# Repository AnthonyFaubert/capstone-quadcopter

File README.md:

# capstone-quadcopter

## Note on creating code for this project
\t It will be to everyone's advantage if we alocate work to this project in different branches based on the work at hand. **DO NOT CHANGE ANYTHING ON THE MASTER BRANCH UNLESS YOU HAVE CONSULTED WITH AT LEAST TWO OTHER GROUP MEMBERS.** Let's save us all some time and sanity, and just use different branches.  Here's a cool trick to making a new branch in your command line/git bash:

```
// This creates a new branch if the name of this branch does not already exist
git branch new_branch_name_here

// This pushes your new branch to the repository (thus, you can actually push
// any changes you make to this branch to the respository).
git push --set-upstream origin new_branch_name_here 

// Switch over to working on the new branch you just made
git checkout new_branch_name_here
```

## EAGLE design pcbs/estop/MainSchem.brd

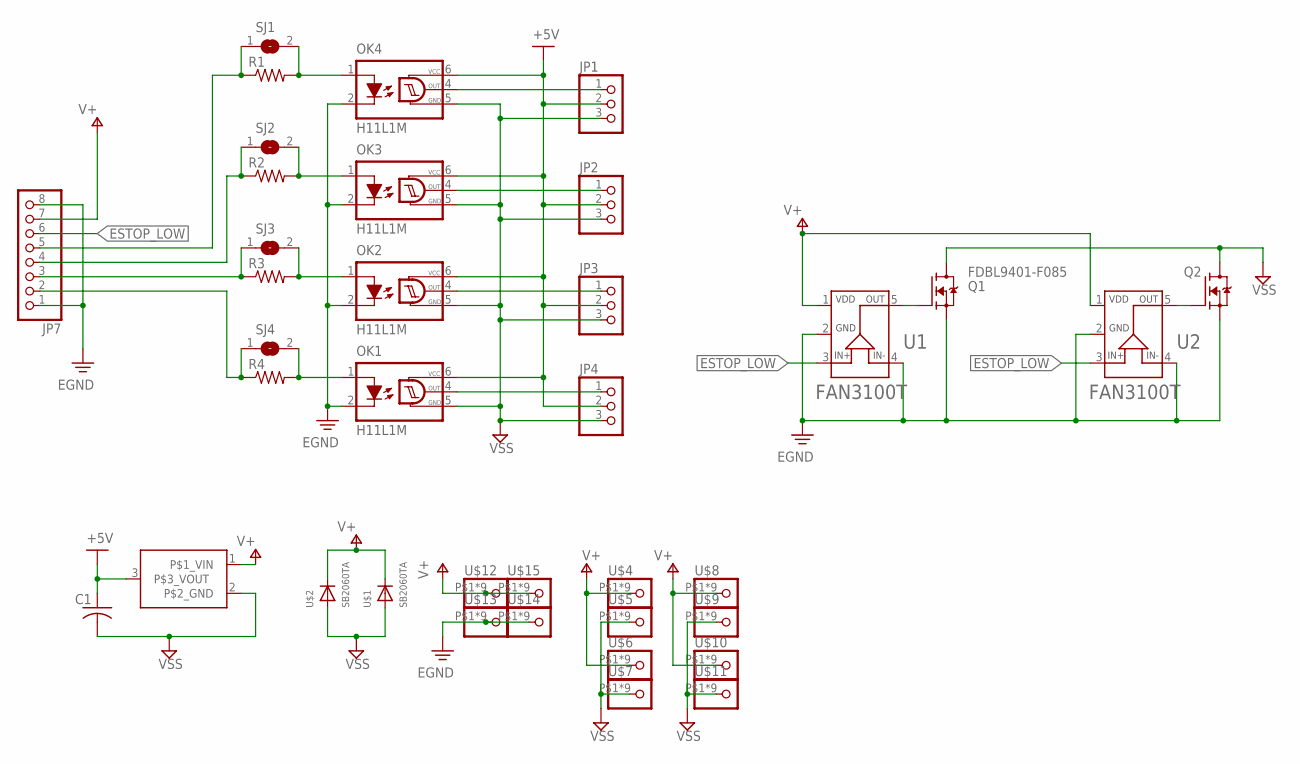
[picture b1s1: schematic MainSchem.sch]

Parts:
C1: C-US025-025X050; C025-025X050
JP1, JP2, JP3, JP4: PINHD-1X3; 1X03
JP7: PINHD-1X8_RIBBONCABLE; 1X08_RIBBONCABLE
OK1, OK2, OK3, OK4: H11L1M; DIL06
Q1, Q2: FDBL9401-F085; MOSFET_FDBL86361-F085
R1, R2, R3, R4: R-US_0204/7; 0204/7
SJ1, SJ2, SJ3, SJ4: SJ
U1, U2: FAN3100T; SOT23-5
U$1, U$2: SB2060TA; C4111-15
U$3: REGULATOR_5V; TO220
U$4, U$5, U$6, U$7, U$8, U$9, U$10, U$11, U$12, U$13, U$14, U$15: HIGH_CURRENT_WIRE_PAD

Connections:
+5V: C1.1, JP1.2, JP2.2, JP3.2, JP4.2, OK1.6 (VCC), OK2.6 (VCC), OK3.6 (VCC), OK4.6 (VCC), U$3.3 (P$3_VOUT)
EGND: JP7.1, JP7.8, OK1.2 (C), OK2.2 (C), OK3.2 (C), OK4.2 (C), Q1.2 (S), Q1.3 (S), Q1.4 (S), Q1.5 (S), Q1.6 (S), Q1.7 (S), Q1.8 (S), Q2.2 (S), Q2.3 (S), Q2.4 (S), Q2.5 (S), Q2.6 (S), Q2.7 (S), Q2.8 (S), U1.2 (GND), U1.4 (IN-), U2.2 (GND), U2.4 (IN-), U$13.P$1, U$13.P$2, U$13.P$3, U$13.P$4, U$13.P$5, U$13.P$6, U$13.P$7, U$13.P$8, U$13.P$9, U$14.P$1, U$14.P$2, U$14.P$3, U$14.P$4, U$14.P$5, U$14.P$6, U$14.P$7, U$14.P$8, U$14.P$9
ESTOP_LOW: JP7.6, U1.3 (IN+), U2.3 (IN+)
unnamed: Q2.1 (G), U2.5 (OUT)
unnamed: OK1.1 (A), R4.2, SJ4.2
unnamed: Q1.1 (G), U1.5 (OUT)
unnamed: JP4.1, OK1.4 (OUT)
unnamed: JP7.2, R4.1, SJ4.1
unnamed: JP3.1, OK2.4 (OUT)
unnamed: JP2.1, OK3.4 (OUT)
unnamed: JP1.1, OK4.4 (OUT)
unnamed: JP7.3, R3.1, SJ3.1
unnamed: OK2.1 (A), R3.2, SJ3.2
unnamed: OK3.1 (A), R2.2, SJ2.2
unnamed: JP7.4, R2.1, SJ2.1
unnamed: OK4.1 (A), R1.2, SJ1.2
unnamed: JP7.5, R1.1, SJ1.1
V+: JP7.7, U1.1 (VDD), U2.1 (VDD), U$1.C, U$2.C, U$3.1 (P$1_VIN), U$4.P$1, U$4.P$2, U$4.P$3, U$4.P$4, U$4.P$5, U$4.P$6, U$4.P$7, U$4.P$8, U$4.P$9, U$6.P$1, U$6.P$2, U$6.P$3, U$6.P$4, U$6.P$5, U$6.P$6, U$6.P$7, U$6.P$8, U$6.P$9, U$8.P$1, U$8.P$2, U$8.P$3, U$8.P$4, U$8.P$5, U$8.P$6, U$8.P$7, U$8.P$8, U$8.P$9, U$10.P$1, U$10.P$2, U$10.P$3, U$10.P$4, U$10.P$5, U$10.P$6, U$10.P$7, U$10.P$8, U$10.P$9, U$12.P$1, U$12.P$2, U$12.P$3, U$12.P$4, U$12.P$5, U$12.P$6, U$12.P$7, U$12.P$8, U$12.P$9, U$15.P$1, U$15.P$2, U$15.P$3, U$15.P$4, U$15.P$5, U$15.P$6, U$15.P$7, U$15.P$8, U$15.P$9
VSS: C1.2, JP1.3, JP2.3, JP3.3, JP4.3, OK1.5 (GND), OK2.5 (GND), OK3.5 (GND), OK4.5 (GND), Q1.9_1 (D), Q1.9_2 (D), Q1.9_3 (D), Q1.9_4 (D), Q2.9_1 (D), Q2.9_2 (D), Q2.9_3 (D), Q2.9_4 (D), U$1.A, U$2.A, U$3.2 (P$2_GND), U$5.P$1, U$5.P$2, U$5.P$3, U$5.P$4, U$5.P$5, U$5.P$6, U$5.P$7, U$5.P$8, U$5.P$9, U$7.P$1, U$7.P$2, U$7.P$3, U$7.P$4, U$7.P$5, U$7.P$6, U$7.P$7, U$7.P$8, U$7.P$9, U$9.P$1, U$9.P$2, U$9.P$3, U$9.P$4, U$9.P$5, U$9.P$6, U$9.P$7, U$9.P$8, U$9.P$9, U$11.P$1, U$11.P$2, U$11.P$3, U$11.P$4, U$11.P$5, U$11.P$6, U$11.P$7, U$11.P$8, U$11.P$9

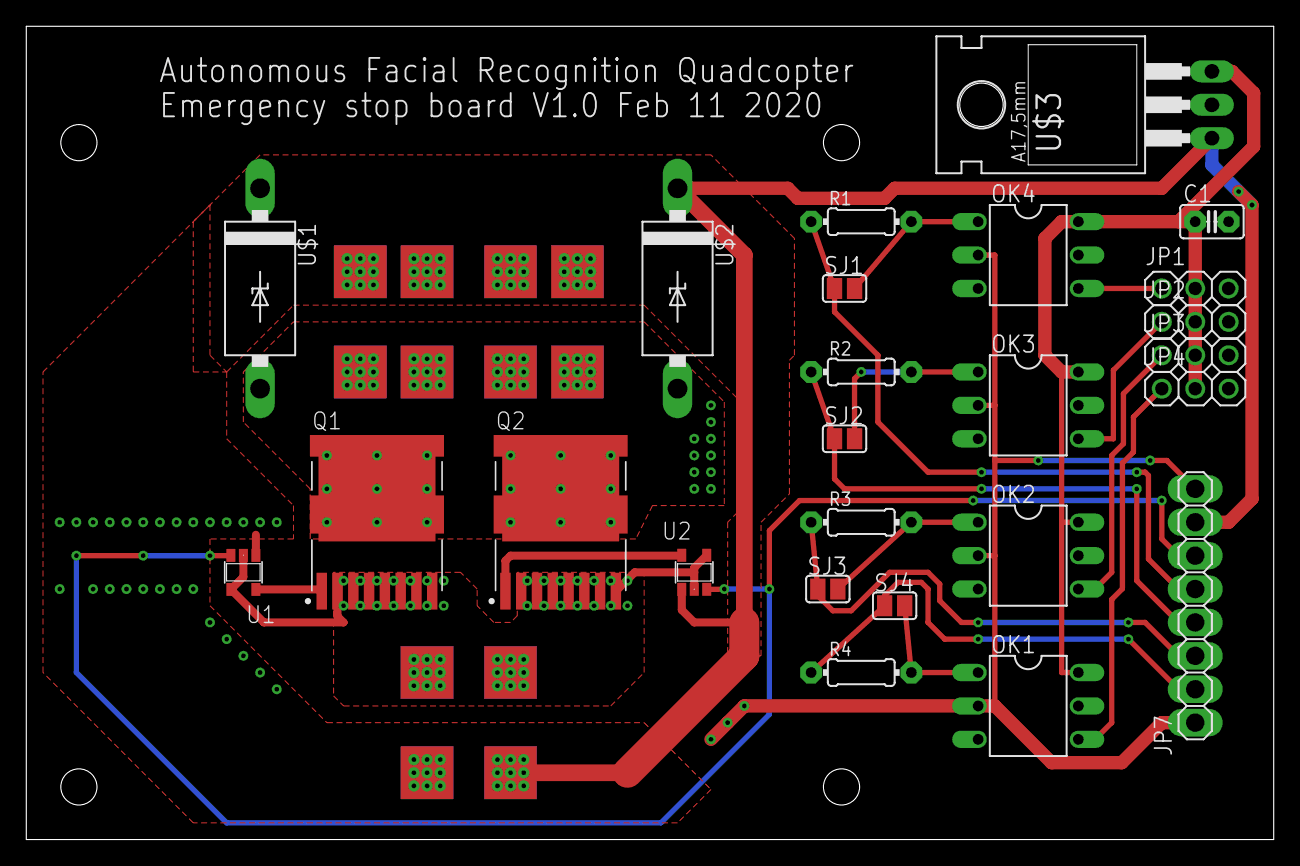
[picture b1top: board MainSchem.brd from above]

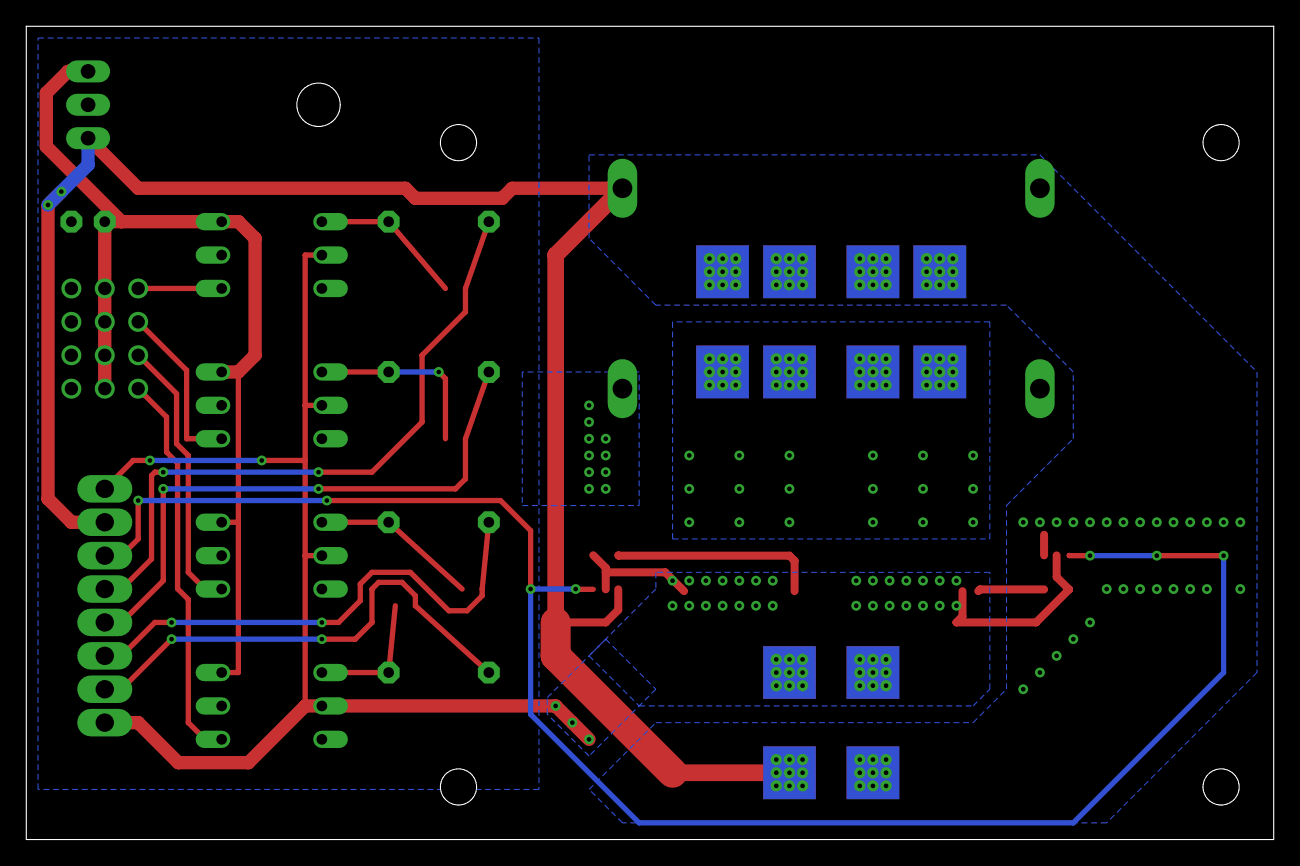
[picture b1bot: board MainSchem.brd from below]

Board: 2 copper layers, 94.9 x 61.8 mm, 41 parts (7 on the bottom side), 19 nets.

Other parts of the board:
U$16, U$17, U$18, U$19: RPI_MOUNTING_HOLE

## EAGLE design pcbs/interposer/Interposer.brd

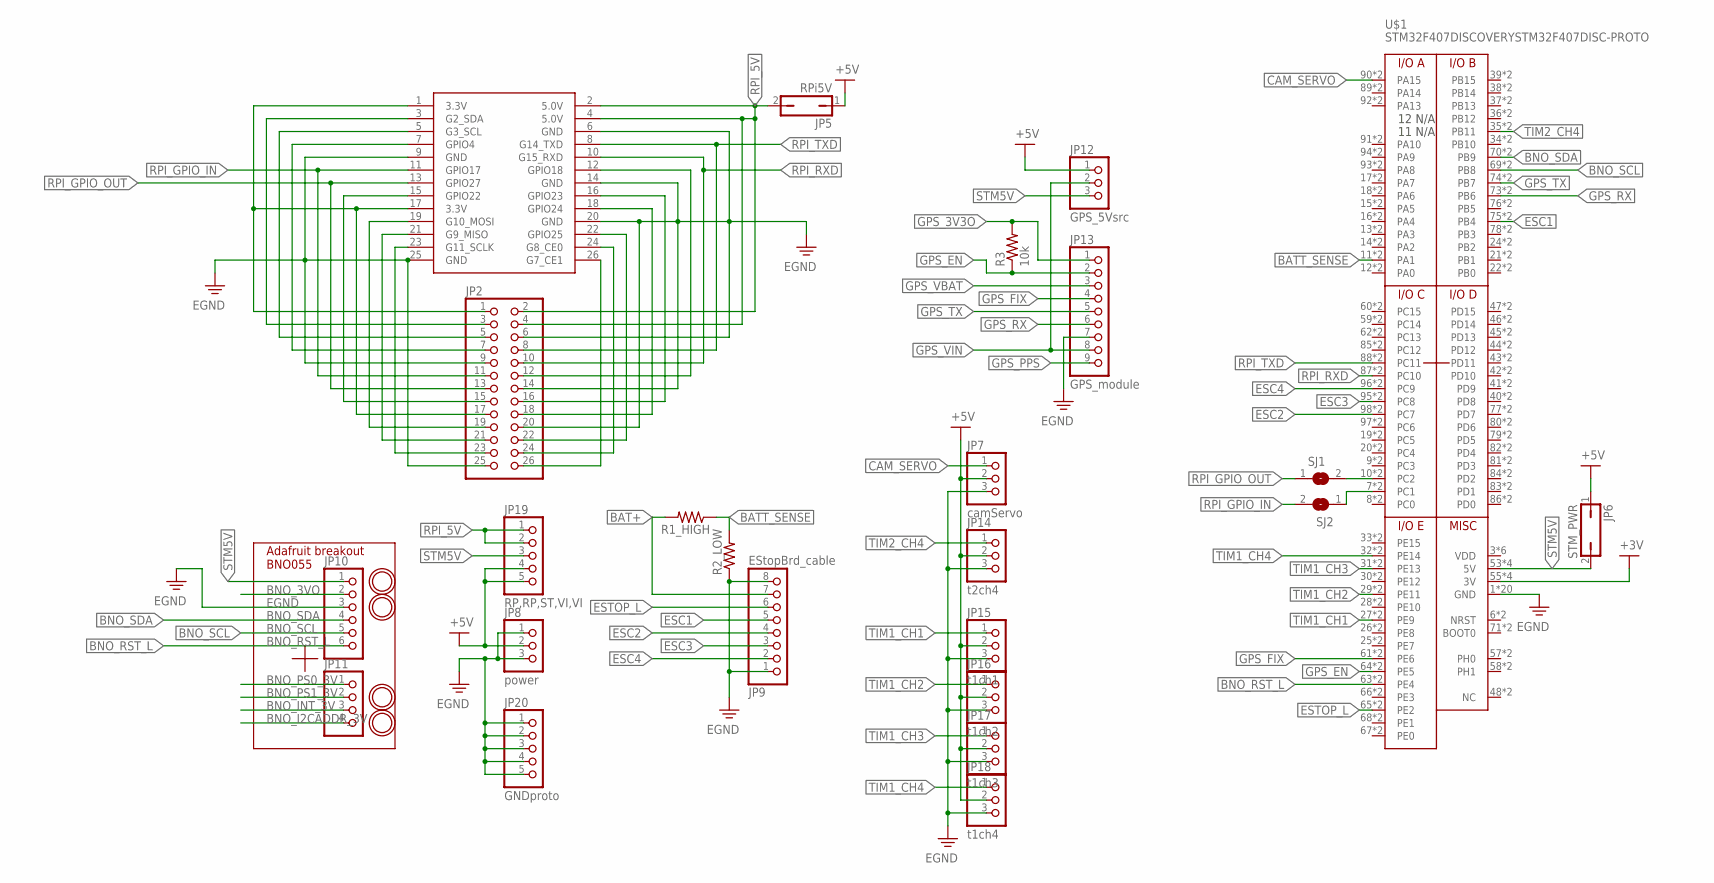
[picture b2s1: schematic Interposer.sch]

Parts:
JP1: MICROBUILDER_RASBERRYPI_IDC
JP2: PINHD-2X13; 2X13
JP5: RPi5V; JP1
JP6: STM_PWR; JP1
JP7: camServo; 1X03
JP8: power; 1X03
JP9: EStopBrd_cable; 1X08_RIBBONCABLE
JP10: HEADER-1X676MIL; 1X06_ROUND_76
JP11: HEADER-1X476MIL; 1X04_ROUND_76
JP12: GPS_5Vsrc; 1X03
JP13: GPS_module; 1X09
JP14: t2ch4; 1X03
JP15: t1ch1; 1X03
JP16: t1ch2; 1X03
JP17: t1ch3; 1X03
JP18: t1ch4; 1X03
JP19: RP,RP,ST,VI,VI; 1X05
JP20: GNDproto; 1X05
R1_HIGH, R2_LOW: R-US_0204/7; 0204/7
R3: 10k; 0204/7
SJ1, SJ2: SJ
U$1: STM32F407DISCOVERYSTM32F407DISC-PROTO; STM32F407DISC_WITH_PROTO_HEADERS
U$29, U$30, U$31, U$32: MOUNTINGHOLE2.5_THICK; MOUNTINGHOLE_2.5_PLATED_THICK

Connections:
3V: U$1.55 (3V), U$1.56 (3V), U$1.153 (3V), U$1.178 (3V)
+5V: JP5.1, JP6.1, JP7.2, JP8.2, JP12.1, JP14.2, JP15.2, JP16.2, JP17.2, JP18.2, JP19.4, JP19.5
BAT+: JP9.7, R1_HIGH.2
BATT_SENSE: R1_HIGH.1, R2_LOW.2, U$1.11 (PA1), U$1.106 (PA1)
BNO_3VO: JP10.2
BNO_I2CADDR_3V: JP11.4
BNO_INT_3V: JP11.3
BNO_PS0_3V: JP11.1
BNO_PS1_3V: JP11.2
BNO_RST_L: JP10.6, U$1.63 (PE4), U$1.157 (PE4)
BNO_SCL: JP10.5, U$1.69 (PB8), U$1.160 (PB8)
BNO_SDA: JP10.4, U$1.70 (PB9), U$1.185 (PB9)
CAM_SERVO: JP7.1, U$1.90 (PA15), U$1.195 (PA15)
EGND: JP1.6 (GND), JP1.9 (GND), JP1.14 (GND), JP1.20 (GND), JP1.25 (GND), JP2.6, JP2.9, JP2.14, JP2.20, JP2.25, JP7.3, JP8.1, JP8.3, JP9.1, JP9.8, JP10.3, JP13.7, JP14.3, JP15.3, JP16.3, JP17.3, JP18.3, JP20.1, JP20.2, JP20.3, JP20.4, JP20.5, R2_LOW.1, U$1.1 (GND), U$1.2 (GND), U$1.5 (GND), U$1.23 (GND), U$1.49 (GND), U$1.50 (GND), U$1.51 (GND), U$1.52 (GND), U$1.99 (GND), U$1.100 (GND), U$1.101 (GND), U$1.103 (GND), U$1.112 (GND), U$1.125 (GND), U$1.126 (GND), U$1.150 (GND), U$1.151 (GND), U$1.175 (GND), U$1.176 (GND), U$1.200 (GND)
ESC1: JP9.5, U$1.75 (PB4), U$1.163 (PB4)
ESC2: JP9.4, U$1.98 (PC7), U$1.199 (PC7)
ESC3: JP9.3, U$1.95 (PC8), U$1.173 (PC8)
ESC4: JP9.2, U$1.96 (PC9), U$1.198 (PC9)
ESTOP_L: JP9.6, U$1.65 (PE2), U$1.158 (PE2)
GPS_3V3O: JP13.1, R3.2
GPS_EN: JP13.2, R3.1, U$1.64 (PE5), U$1.182 (PE5)
GPS_FIX: JP13.4, U$1.61 (PE6), U$1.156 (PE6)
GPS_PPS: JP13.9
GPS_RX: JP13.6, U$1.73 (PB6), U$1.162 (PB6)
GPS_TX: JP13.5, U$1.74 (PB7), U$1.187 (PB7)
GPS_VBAT: JP13.3
GPS_VIN: JP12.2, JP13.8
unnamed: JP1.23 (G11_SCLK), JP2.23
unnamed: JP1.21 (G9_MISO), JP2.21
unnamed: JP1.19 (G10_MOSI), JP2.19
unnamed: JP1.15 (GPIO22), JP2.15
unnamed: JP1.7 (GPIO4), JP2.7
unnamed: JP1.5 (G3_SCL), JP2.5
unnamed: JP1.3 (G2_SDA), JP2.3
unnamed: JP1.26 (G7_CE1), JP2.26
unnamed: JP1.24 (G8_CE0), JP2.24
unnamed: JP1.22 (GPIO25), JP2.22
unnamed: JP1.18 (GPIO24), JP2.18
unnamed: JP1.16 (GPIO23), JP2.16
unnamed: JP1.12 (GPIO18), JP2.12
unnamed: SJ1.2, U$1.10 (PC2), U$1.130 (PC2)
unnamed: SJ2.1, U$1.7 (PC1), U$1.104 (PC1)
RPI_3V3: JP1.1 (3.3V), JP1.17 (3.3V), JP2.1, JP2.17
RPI_5V: JP1.2 (5.0V), JP1.4 (5.0V), JP2.2, JP2.4, JP5.2, JP19.1, JP19.2
RPI_GPIO_IN: JP1.11 (GPIO17), JP2.11, SJ2.2
RPI_GPIO_OUT: JP1.13 (GPIO27), JP2.13, SJ1.1
RPI_RXD: JP1.10 (G15_RXD), JP2.10, U$1.87 (PC10), U$1.169 (PC10)
RPI_TXD: JP1.8 (G14_TXD), JP2.8, U$1.88 (PC11), U$1.194 (PC11)
STM5V: JP6.2, JP10.1, JP12.3, JP19.3, U$1.53 (5V), U$1.54 (5V), U$1.152 (5V), U$1.177 (5V)
TIM1_CH1: JP15.1, U$1.27 (PE9), U$1.114 (PE9)
TIM1_CH2: JP16.1, U$1.29 (PE11), U$1.115 (PE11)
TIM1_CH3: JP17.1, U$1.31 (PE13), U$1.116 (PE13)
TIM1_CH4: JP18.1, U$1.32 (PE14), U$1.141 (PE14)
TIM2_CH4: JP14.1, U$1.35 (PB11), U$1.118 (PB11)

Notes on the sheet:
Adafruit breakout BNO055

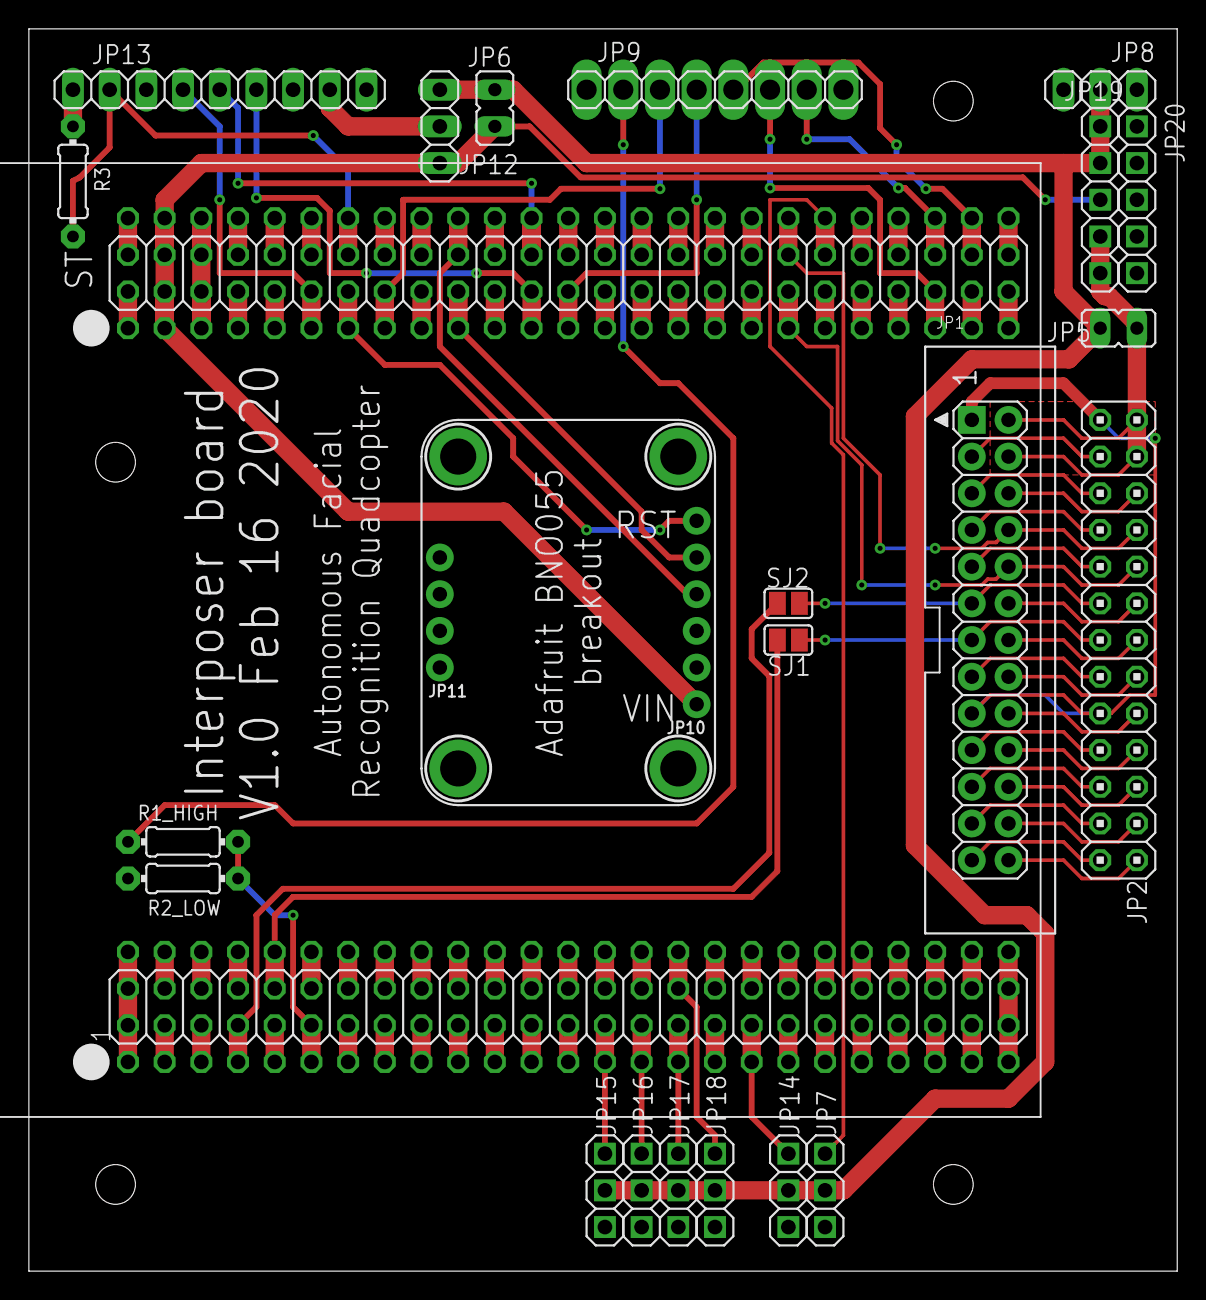
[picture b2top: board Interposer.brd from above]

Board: 2 copper layers, 79.5 x 86.0 mm, 32 parts (0 on the bottom side), 47 nets.

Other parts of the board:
U$2, U$3, U$4, U$5: RPI_MOUNTING_HOLE

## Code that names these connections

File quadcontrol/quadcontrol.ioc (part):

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Mcu.Name=STM32F407V(E-G)Tx
Mcu.Package=LQFP100
Mcu.UserName=STM32F407VGTx
PA0-WKUP.GPIOParameters=GPIO_PuPd,GPIO_Label,GPIO_ModeDefaultEXTI
PA0-WKUP.GPIO_Label=B1 [Blue PushButton]
PA0-WKUP.GPIO_ModeDefaultEXTI=GPIO_MODE_EVT_RISING
PA0-WKUP.GPIO_PuPd=GPIO_NOPULL
PA0-WKUP.Signal=GPXTI0
PA1.Signal=ADCx_IN1
PA10.GPIOParameters=GPIO_Speed,GPIO_PuPd,GPIO_Label,GPIO_Mode
PA10.GPIO_Label=OTG_FS_ID
PA10.GPIO_Mode=GPIO_MODE_AF_PP
PA10.GPIO_PuPd=GPIO_NOPULL
PA10.GPIO_Speed=GPIO_SPEED_FREQ_LOW
PA10.Signal=USB_OTG_FS_ID
PA11.GPIOParameters=GPIO_Speed,GPIO_PuPd,GPIO_Label,GPIO_Mode
PA11.GPIO_Label=OTG_FS_DM
PA11.GPIO_Mode=GPIO_MODE_AF_PP
PA11.GPIO_PuPd=GPIO_NOPULL
PA11.GPIO_Speed=GPIO_SPEED_FREQ_LOW
PA11.Signal=USB_OTG_FS_DM
PA12.GPIOParameters=GPIO_Speed,GPIO_PuPd,GPIO_Label,GPIO_Mode
PA12.GPIO_Label=OTG_FS_DP
PA12.GPIO_Mode=GPIO_MODE_AF_PP
PA12.GPIO_PuPd=GPIO_NOPULL
PA12.GPIO_Speed=GPIO_SPEED_FREQ_LOW
PA12.Signal=USB_OTG_FS_DP
PA13.GPIOParameters=GPIO_Label
PA13.GPIO_Label=SWDIO
PA13.Mode=Serial_Wire
PA13.Signal=SYS_JTMS-SWDIO
PA14.GPIOParameters=GPIO_Label
PA14.GPIO_Label=SWCLK
PA14.Mode=Serial_Wire
PA14.Signal=SYS_JTCK-SWCLK
PA15.GPIOParameters=GPIO_Label
PA15.GPIO_Label=Cam
PA15.Signal=S_TIM2_CH1_ETR
PA2.Mode=Asynchronous
PA2.Signal=USART2_TX
PA4.GPIOParameters=GPIO_Speed,GPIO_PuPd,GPIO_Label,GPIO_Mode
PA4.GPIO_Label=I2S3_WS [CS43L22_LRCK]
PA4.GPIO_Mode=GPIO_MODE_AF_PP
PA4.GPIO_PuPd=GPIO_NOPULL
PA4.GPIO_Speed=GPIO_SPEED_FREQ_LOW
PA4.Signal=I2S3_WS
PA5.GPIOParameters=GPIO_Speed,GPIO_PuPd,GPIO_Label,GPIO_Mode
PA5.GPIO_Label=SPI1_SCK [LIS302DL_SCL/SPC]
PA5.GPIO_Mode=GPIO_MODE_AF_PP
PA5.GPIO_PuPd=GPIO_NOPULL
PA5.GPIO_Speed=GPIO_SPEED_FREQ_LOW
PA5.Signal=SPI1_SCK
PA6.GPIOParameters=GPIO_Speed,GPIO_PuPd,GPIO_Label,GPIO_Mode
PA6.GPIO_Label=SPI1_MISO [LIS302DL_SDO]
PA6.GPIO_Mode=GPIO_MODE_AF_PP
PA6.GPIO_PuPd=GPIO_NOPULL
PA6.GPIO_Speed=GPIO_SPEED_FREQ_LOW
PA6.Signal=SPI1_MISO
PA7.GPIOParameters=GPIO_Speed,GPIO_PuPd,GPIO_Label,GPIO_Mode
PA7.GPIO_Label=SPI1_MOSI [LIS302DL_SDA/SDI/SDO]
PA7.GPIO_Mode=GPIO_MODE_AF_PP
PA7.GPIO_PuPd=GPIO_NOPULL
PA7.GPIO_Speed=GPIO_SPEED_FREQ_LOW
PA7.Signal=SPI1_MOSI
PA9.GPIOParameters=GPIO_PuPd,GPIO_Label,GPIO_Mode
PA9.GPIO_Label=VBUS_FS
PA9.GPIO_Mode=GPIO_MODE_INPUT
PA9.GPIO_PuPd=GPIO_NOPULL
PA9.Signal=USB_OTG_FS_VBUS
PB10.GPIOParameters=GPIO_Speed,GPIO_PuPd,GPIO_Label,GPIO_Mode
PB10.GPIO_Label=CLK_IN [MP45DT02_CLK]
PB10.GPIO_Mode=GPIO_MODE_AF_PP
PB10.GPIO_PuPd=GPIO_NOPULL
PB10.GPIO_Speed=GPIO_SPEED_FREQ_LOW
PB10.Signal=I2S2_CK
PB11.Signal=S_TIM2_CH4
PB2.Signal=GPIO_Input
PB3.GPIOParameters=GPIO_Label
PB3.GPIO_Label=SWO
PB3.Signal=SYS_JTDO-SWO
PB6.Mode=Asynchronous
PB6.Signal=USART1_TX
PB7.Mode=Asynchronous
PB7.Signal=USART1_RX
PB8.Mode=I2C
PB8.Signal=I2C1_SCL
PB9.GPIOParameters=GPIO_Speed,GPIO_PuPd,GPIO_Label,GPIO_Mode
PB9.GPIO_Label=Audio_SDA [CS43L22_SDA]
PB9.GPIO_Mode=GPIO_MODE_AF_OD
PB9.GPIO_PuPd=GPIO_NOPULL
PB9.GPIO_Speed=GPIO_SPEED_FREQ_LOW
PB9.Mode=I2C
PB9.Signal=I2C1_SDA
PC0.GPIOParameters=GPIO_Speed,PinState,GPIO_PuPd,GPIO_Label
PC0.GPIO_Label=OTG_FS_PowerSwitchOn
PC0.GPIO_PuPd=GPIO_NOPULL
PC0.GPIO_Speed=GPIO_SPEED_FREQ_LOW
PC0.PinState=GPIO_PIN_SET
PC0.Signal=GPIO_Output
PC1.GPIOParameters=GPIO_Label
PC1.GPIO_Label=toRPi
PC1.Signal=GPIO_Output
PC10.Mode=Asynchronous
PC10.Signal=USART3_TX
PC11.Mode=Asynchronous
PC11.Signal=USART3_RX
PC12.GPIOParameters=GPIO_Speed,GPIO_PuPd,GPIO_Label,GPIO_Mode
PC12.GPIO_Label=I2S3_SD [CS43L22_SDIN]
PC12.GPIO_Mode=GPIO_MODE_AF_PP
PC12.GPIO_PuPd=GPIO_NOPULL
PC12.GPIO_Speed=GPIO_SPEED_FREQ_LOW
PC12.Signal=I2S3_SD
PC14-OSC32_IN.GPIOParameters=GPIO_Label
PC14-OSC32_IN.GPIO_Label=PC14-OSC32_IN
PC14-OSC32_IN.Mode=LSE-External-Oscillator
PC14-OSC32_IN.Signal=RCC_OSC32_IN
PC15-OSC32_OUT.GPIOParameters=GPIO_Label
PC15-OSC32_OUT.GPIO_Label=PC15-OSC32_OUT
PC15-OSC32_OUT.Mode=LSE-External-Oscillator
PC15-OSC32_OUT.Signal=RCC_OSC32_OUT
PC2.GPIOParameters=GPIO_Label
PC2.GPIO_Label=fromRPi
PC2.Signal=GPIO_Input
PC3.GPIOParameters=GPIO_Speed,GPIO_PuPd,GPIO_Label,GPIO_Mode
PC3.GPIO_Label=PDM_OUT [MP45DT02_DOUT]
PC3.GPIO_Mode=GPIO_MODE_AF_PP
PC3.GPIO_PuPd=GPIO_NOPULL
PC3.GPIO_Speed=GPIO_SPEED_FREQ_LOW
PC3.Signal=I2S2_SD
PC7.Signal=S_TIM3_CH2
PC8.Signal=S_TIM3_CH3
PC9.Signal=S_TIM3_CH4
PD12.GPIOParameters=GPIO_Speed,GPIO_PuPd,GPIO_Label
PD12.GPIO_Label=LD4 [Green Led]
PD12.GPIO_PuPd=GPIO_NOPULL
PD12.GPIO_Speed=GPIO_SPEED_FREQ_LOW
PD12.Signal=GPIO_Output
PD13.GPIOParameters=GPIO_Speed,GPIO_PuPd,GPIO_Label
PD13.GPIO_Label=LD3 [Orange Led]
PD13.GPIO_PuPd=GPIO_NOPULL
PD13.GPIO_Speed=GPIO_SPEED_FREQ_LOW
PD13.Signal=GPIO_Output
PD14.GPIOParameters=GPIO_Speed,GPIO_PuPd,GPIO_Label
PD14.GPIO_Label=LD5 [Red Led]
PD14.GPIO_PuPd=GPIO_NOPULL
PD14.GPIO_Speed=GPIO_SPEED_FREQ_LOW
PD14.Signal=GPIO_Output
PD15.GPIOParameters=GPIO_Speed,GPIO_PuPd,GPIO_Label
PD15.GPIO_Label=LD6 [Blue Led]
PD15.GPIO_PuPd=GPIO_NOPULL
PD15.GPIO_Speed=GPIO_SPEED_FREQ_LOW
PD15.Signal=GPIO_Output
PD4.GPIOParameters=GPIO_Speed,GPIO_PuPd,GPIO_Label
PD4.GPIO_Label=Audio_RST [CS43L22_RESET]
PD4.GPIO_PuPd=GPIO_NOPULL
PD4.GPIO_Speed=GPIO_SPEED_FREQ_LOW
PD4.Signal=GPIO_Output
PD5.GPIOParameters=GPIO_PuPd,GPIO_Label,GPIO_Mode
PD5.GPIO_Label=OTG_FS_OverCurrent
PD5.GPIO_Mode=GPIO_MODE_INPUT
PD5.GPIO_PuPd=GPIO_NOPULL
PD5.Signal=GPIO_Input
PD6.Mode=Asynchronous
PD6.Signal=USART2_RX
PE1.GPIOParameters=GPIO_PuPd,GPIO_Label,GPIO_ModeDefaultEXTI
PE1.GPIO_Label=MEMS_INT2 [LIS302DL_INT2]
PE1.GPIO_ModeDefaultEXTI=GPIO_MODE_EVT_RISING
PE1.GPIO_PuPd=GPIO_NOPULL
PE1.Signal=GPXTI1
PE11.Signal=S_TIM1_CH2
PE13.Signal=S_TIM1_CH3
PE14.Signal=S_TIM1_CH4
PE2.GPIOParameters=GPIO_Speed,PinState,GPIO_Label
PE2.GPIO_Label=EStop_L
PE2.GPIO_Speed=GPIO_SPEED_FREQ_MEDIUM
PE2.PinState=GPIO_PIN_SET
PE2.Signal=GPIO_Output
PE3.Signal=GPIO_Output
PE4.GPIOParameters=GPIO_Label
PE4.GPIO_Label=IMU_RST_L
PE4.Signal=GPIO_Output
PE5.GPIOParameters=PinState,GPIO_Label,GPIO_ModeDefaultOutputPP
PE5.GPIO_Label=GPS_EN
PE5.GPIO_ModeDefaultOutputPP=GPIO_MODE_OUTPUT_OD
PE5.PinState=GPIO_PIN_SET
PE5.Signal=GPIO_Output
PE6.GPIOParameters=GPIO_Label
PE6.GPIO_Label=GPS_FIX
PE6.Signal=GPIO_Input
PE9.Signal=S_TIM1_CH1
PH0-OSC_IN.GPIOParameters=GPIO_Label
PH0-OSC_IN.GPIO_Label=PH0-OSC_IN
PH0-OSC_IN.Mode=HSE-External-Oscillator
PH0-OSC_IN.Signal=RCC_OSC_IN
PH1-OSC_OUT.GPIOParameters=GPIO_Label
PH1-OSC_OUT.GPIO_Label=PH1-OSC_OUT
PH1-OSC_OUT.Mode=HSE-External-Oscillator
PH1-OSC_OUT.Signal=RCC_OSC_OUT
RCC.HSE_VALUE=8000000
RCC.SYSCLKFreq_VALUE=168000000
RCC.SYSCLKSource=RCC_SYSCLKSOURCE_PLLCLK
board=STM32F407G-DISC1
boardIOC=true

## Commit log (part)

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2020-01-21 The Main Workspace we'll be using is now here. We will be using IAR Workbench for this project. A template project has been uploaded along with the workspace.
2020-01-21 Reorganized project for the sake of our collective sanity
2020-01-21 Quick correction to README
2020-01-21 Changed driver for 'mainWorkspace' to suit needs of STM32F407VG Dev board
2020-01-21 Added skeleton code for my parts. I need to fill out PID.cpp and MotorDriver.cpp, and PID.h just needs rotation/thrust command inputs.
2020-01-22 Added the git checkout command to the instructions for a new branch.
2020-01-23 Quick change to debug folder
2020-01-23 Major setup update. CubeMx used to generate basic project structure. Using this as a skeleton in new project labeled "STM_ExternalController." Separate directory for worked-on code is called "WorkSta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
2020-01-23 Used CubeMX to create register assignments, interrupts, and DMA transfer setup for SPI transaction. Looking make new branch to setup Quadcopter board.
2020-01-23 Update to master: currently using IARWorkbench for external-controller MCU. So far, everything is working as expected. Have been unable to upload to board, but that's due to a lack of board.
2020-01-23 Correction to .gitignore
2020-01-24 Moved 'sertest.py' into separate directory
2020-01-25 Work for 01/24/2020 done for now. USART is working properly, and interrupt functionality is incredibly fast. I am content with this design thus far.
2020-01-26 A few more updates have been made. Particularly, DMA interrupt succesfully implemented, and RX buffer setup (untested). Look to figuring out how to setup SPI
2020-01-28 controller test
2020-01-28 changed cont test
2020-01-28 adding file controller.py
2020-01-29 working byte transfer
2020-01-30 Ready to start working on SPI. STMCubeMX churned out (hopefully) proper register settings for SPI. Test using digital logic analyzer to follow
2020-01-31 Configuration for SPI coming along. Setting up write/read functions for CC1101 device. Hopefully will be able to test later.
2020-01-31 Made changes to main, then found USB isn't instantiated properly.
2020-01-31 Attempts to make USB VCOM work. Unsuccessful so far.
2020-02-01 Added BNO project instructions
2020-02-01 BNO055 gives data over USB with PWM stuff set up!
2020-02-01 Everything has compiled and a basic library for the CC1101 has been created. Looking now to test it out in the lab.
2020-02-03 Added change to accel.c so that we can get stuff other than accelerometer data out. Updated the scratch instructions.
2020-02-03 Fixed a signed vs unsigned bug in my IMU read functions. Gyro and Quaternion data appears reasonable now.
2020-02-03 Quaternion calculations appear to be working now. I seem to be able to get roll,pitch,yaw commands that bring the device to a reasonable orientation when followed.
2020-02-03 Camera testing
2020-02-03 face landmark data added
2020-02-04 Changed pinout of I2C and PWM to work better with minimal pin headers. Fixed syntax to allow compiling, but no actual PID progress yet.
2020-02-05 PID code almost complete; need individual thrust ranges for motors. Tons of tuning still required.
2020-02-06 USART6 and USART3 ready to roll. SPI still in progress, looking to overlook DMA and use direct transfers instead.
2020-02-06 Changed buffer size from 8 to 10 for "ReturnToSender" functions
2020-02-06 Partial success.
2020-02-06 Update .gitignore to make gitbash happy
2020-02-06 ras pi controller code
2020-02-06 PID working reasonably. Pitch&roll gains are tuned for this max thrust. RX from RPi working hacky and unreliably to a currently unusable extent.
2020-02-07 Changed to a packet-based communication system. Added a script to print out packets from debug.txt.
2020-02-07 Update to .gitignore for the sake of our sanity. Looking to work on SPI now.
2020-02-07 Most of the way through adding trim and joystick logic.
2020-02-11 Turns out bug was in Python. Quad now responds to joystick, but it seems very inconsistent in its response.
2020-02-11 Added E-stop board project contents so far. Updated gitignore for Eagle files.
2020-02-11 Modified camtest.py
    Added timing functions to camtest.py. Times how long an image capture takes, how long it takes to return the euler vector, and how long it takes to display the image on the screen.
2020-02-12 Imported RPi mounting holes from one of my previous projects. Added RPi-compatible mounting holes to E-stop board.
2020-02-12 Eagle project changed when the editor closed.
2020-02-12 Was having problems with JLCPCB gerber viewer. Still having those problems, but their board preview seems to work ok, and it works in a different gerber viewer, so I ordered them anyways. This commit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
2020-02-12 Fixed two major bugs in joystick->quaternion logic.
2020-02-13 Joystick quaternion values appear to be correct now!
2020-02-13 Fixed a bug where throttle was ignored. It flew! It was unstable before, so I upped the derivative gain 30%. TBD how much better it flies.
2020-02-13 Updated PID gains to improve stability at this higher max throttle. Seems stable.
2020-02-16 Made the STM32 part, imported the RPi connector part, modified the BNO breakout board into a design block, and made a large portion of the schematic.
2020-02-16 Added a couple extra prototyping headers.
2020-02-16 Working on version of stm32 device with proto headers to simplify schematic.
2020-02-16 Working through layout. Fixed a schematic bug and improved a few things.
2020-02-16 Eagle project closed properly. Ordered interposer board.
2020-02-17 Making sure there are no merge errors when Griffin tries to add new cascade folder from his computer
2020-02-17 haar.py updated and works using piCamera to detect faces and create bounding box
2020-02-17 Moved UART RX FIFO handling stuff into Uart3 module with a callback into quadcontrol.
2020-02-17 Moved direct motor control and button interactions to MiscPeripherals module.
2020-02-18 Moved vector & quaternion math to VectQuatMath module.
2020-02-18 Renamed accel module to IMU module, and moved get functions for orientation & gyro data into it.
2020-02-18 Removed lots of left over stuff. Finished cleaning up code.
2020-02-19 Added green box in haar.py for facial tracking
2020-02-20 Updated haar.py to include an initialization phase.
    The initialization phase waits until tit detects a face before entering the main while loop now.
2020-02-20 Update to controller.py
    Added connection() function and removed extra comments
2020-02-22 Increased e-stop <-> interposer ribbon cable drill size to make soldering the ribbon cable easier in future versions.
2020-02-24 Added socket and image rotation capabilities
2020-02-25 Added code to allow receiving bytes from the USB serial port.
2020-02-26 Fixed the UART RX bug. The UART was going into panic mode when it got data before the DMA was configured, and the solution was to clear the error by reading two special registers.
2020-02-27 I think I fixed the quaternion math. TBD.
2020-02-27 Fixed the RX shift problem by forcing the compiler to not be stupid using volatile, also fixed a separate bug.
2020-02-27 Removed USB CDC because of large (~30%) program space usage. Enabled ADC, but haven't used it due to lack of e-stop board.
2020-02-27 Added gyro adjustments.
2020-02-27 Committed missing gyro correction line in Quadcontrol.c. Fixed timeout message. All PID pos/neg signs should be correct now. Ready to re-tune PID.
2020-02-27 Added gyro value upper limits and increased derivative gains.
2020-02-27 Converted joystick & trim roll/pitch to quadcopter reference frame. Fixed the trim not working bug. Getting the joystick values now automatically includes the trim.
2020-02-27 Added many features to haar.py and controller.py for upcoming phase 2 demo. Both need to be tested.
2020-02-28 Removed leftover USB RX buffer. Added precision data logging feature. Added (currently unused) low pass filter function. Needs typo debugging.
2020-02-28 Added Octave script for displaying gyro data readout.
2020-02-28 Fixed bugs in logging printut. Still might need to deal with log overruns.
2020-02-29 Logging is now resettable and no longer e-stops at the end of the log.
2020-02-29 Drastically improved showdat script. Now has a headless mode for generating plot images.
2020-02-29 Improved log printout resettability.
2020-02-29 Decided motor error logging could be made redundant by increasing motor value printout precision and fixing a bug that clipped motor values before logging them.
2020-02-29 Commiting edited haar.py and controller.py, 2.29
2020-02-29 Fixed typos and added throttle logging.
2020-02-29 deleted unecessary comments in controller.py
2020-03-01 Made log printout independent of UART speed. Re-organized raw gyro logging.
2020-03-01 Added single roll step response and motor map check experiments.
2020-03-01 Adjusted SingleStepRoll experiment and converted it to pitch experiment. Running it right after this commit.
2020-03-02 Made the SingleStepPitch experiment's results much more obvious. Our feedback delay is between 40 and 60 ms.
2020-03-02 Moved experiments to their own file and added the sinewave experiment.
2020-03-02 Log now takes raw pErrors before limiting.
2020-03-02 Fixed bug in sine wave experiment and set the amplitude to what we used.
2020-03-02 Fixed a bug in limitGyros that would disable gyro feedback when the limits weren't defined.
2020-03-02 Upped UART baud rate to 460800. Almost 100% stable.
2020-03-02 Commented out sine experiment. Remember to remove pErrorStep code. Stable gains were P=-0.2 D=-0.001. Current gains haven't been properly tested, but seem ok.
2020-03-02 Cleaned up code for controller.py and haar.py
    Included conditional use of sockets so we just need to change one boolean to true instead of uncommenting all uses of the socket
2020-03-02 Tweaked gains and disabled pErrorStep.
2020-03-03 Made drastic changes to p-error computations and joystick quaternions. Removed all yaw. Added joystick quaternion and joystick value logging.
2020-03-03 Fixed a bug in QuatRotateVector() and moved that function to VectQuatMath module.
2020-03-04 Split proportional error function into two: quaternion difference calc and quat2euler. quat2euler is empty for now. Reformatted realtime printouts.
2020-03-04 Added Quaternion to Euler conversion math from Wikipedia.
2020-03-04 FIXED A BUG IN the QuaternionsMultiply FUNCTION THAT ONLY BROKE THE PROPORTIONAL ERRORS SOMETIMES BUT NOTHING ELSE! VICTORY IS NEAR!
2020-03-05 QuaternionsMultiply actually wasn't changed, I just moved some terms around. This time I swapped the order that I multiply the actual2Earth and earth2Desired quaternions and now the results seem sane.
2020-03-05 All bugs are squashed! PID could use more tuning, but it's not bad on a string from the ceiling.
2020-03-05 Incorporated new control scheme.
2020-03-06 Downloaded http://quaternions.online/ into our project.
2020-03-06 Added the current state of the website.
2020-03-06 Moved CSS into its own file. Removed old index2.html file.
2020-03-06 Added conditional to check if we have received a full packet from haar.py and added initialization values for x, y, and w errors and derivatives
2020-03-06 Moved quat_page to status.html and merged it with quat.html. Moved js to its own folder.
2020-03-06 Copied Quaternions.online main.js to quaternionsonline.js and tried to use it directly on status page.
2020-03-06 Fixed rendering orientation to make viewing quadcopter orientation much easier.
2020-03-06 Reordered things on the status page.
2020-03-06 Minor status page improvements.
2020-03-07 Re-worded some things
2020-03-07 Fixed minor bugs in new control scheme. Feedback looks correct.
2020-03-07 Commented out something we're not using.
2020-03-07 Added latestDataDump.py CGI script to make getting just the matlab data from the last flight easier.
2020-03-07 Added script to grab the latest matlab data.
2020-03-07 Fixed a logging bug that used non-raw gyro data. Upped PID rate to 100Hz.
2020-03-08 Fixed some computations in showdat.m and added motor clipping computation.
2020-03-08 Sine wave sweep experiment.
2020-03-09 Commit of haar2.py and controller.py from test day
2020-03-13 Added convenience scripts we've been using and the RPi install log.
2020-03-13 Comments added
    Comments added in haar2.py and controller.py for readability and for submission

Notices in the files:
parts and their libraries:
microbuilder: This work is placed in the public domain, and may be freely used for commercial and non-commercial work with the following conditions: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
